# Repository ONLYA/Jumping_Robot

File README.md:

# Jumping_Robot
A robot that is like the RC Jumper in Watch Dogs 2

The updates of the project are in [my blog](https://www.300-300-300-300.space/blog/5/).

In the video above, you can find that there are several functions for the jumpers to achieve:
* Compact
* RF controlled
* "Tank" moving
* Jumping (with "enhanced spring", it can jump over a wall)
* Rotation-free web camera
* Robot arms
* Middle-Man network
* Automatic recognizing the 3D position

There are more functions that it has:
* Items dropping (unlikely to be considered this time!)
* Broadcasting some sound (Maybe included)

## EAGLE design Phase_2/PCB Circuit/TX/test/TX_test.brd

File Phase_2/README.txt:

# PHASE 2
+----------------------------------------------------------+
|                 PHASE 2 - REMOTE CONTROL                 |
+----------------------------------------------------------+
|                  Overview Block Diagram                  |
+----------------------------------------------------------+
 Si4663F30        Si4663F30                MSP430G2553IN20
+----------+   +-------------+          +------------------+
|          <---+             |8-bit GPIO|                  |
| Reciever |RF | Transmitter <----------+ Data Auto-Sender |
|          +--->             <----------+                  |
+----------+   +----------^--+State_SEL +---+----^---------+
                          |                 |    |
                          +-----------------+    |
+---------------------------+  INT/DONE          |
|    Possible Ideas:        |           +--------+---------+
| 1. The computer only      |           |     Joystick     |
|    sends the image        |           |    (Via ADC10)   |
|    coordination data      |           |                  |
| 2. Computer processes     |           +------------------+
|    the data & sends       |           |     Computer     |
|    the preocessed data.   |           |    (Via SPI)     |
|                           |           |                  |
+---------------------------+           +------------------+
+----------------------------------------------------------+
|               Si4663 Interfacing Diagram                 |
+----------------------------------------------------------+
+--------+  +----------------------------------------------+
|        <==>SPI                                           |
| Si4663 |  |                            MSP430G2553       |
|        +-->INT                                           |
+--------+  +----------------------------------------------+
+----------------------------------------------------------+
## API
All of the API functions processed by MSP430 for Si4663 are
regarded to the official programming guide, which can be
downloaded in the current folder.
## Ideas
The basic ideas of this phase can be summarised into points:
1. Special modules for RF transcieving
2. A specialised module to send the sensed data to the RF module
## Components
1. [Si4663F30](https://www.aliexpress.com/item/32816312908.html "Link to buy Si4663F30, a more powerful RF module")
2. MSP430G2553IN20
3. Joystick
4. Computer
5. [USB-to-SPI interface] ... Not found one, try UART probably.
## Test
Still waiting for the delivery...

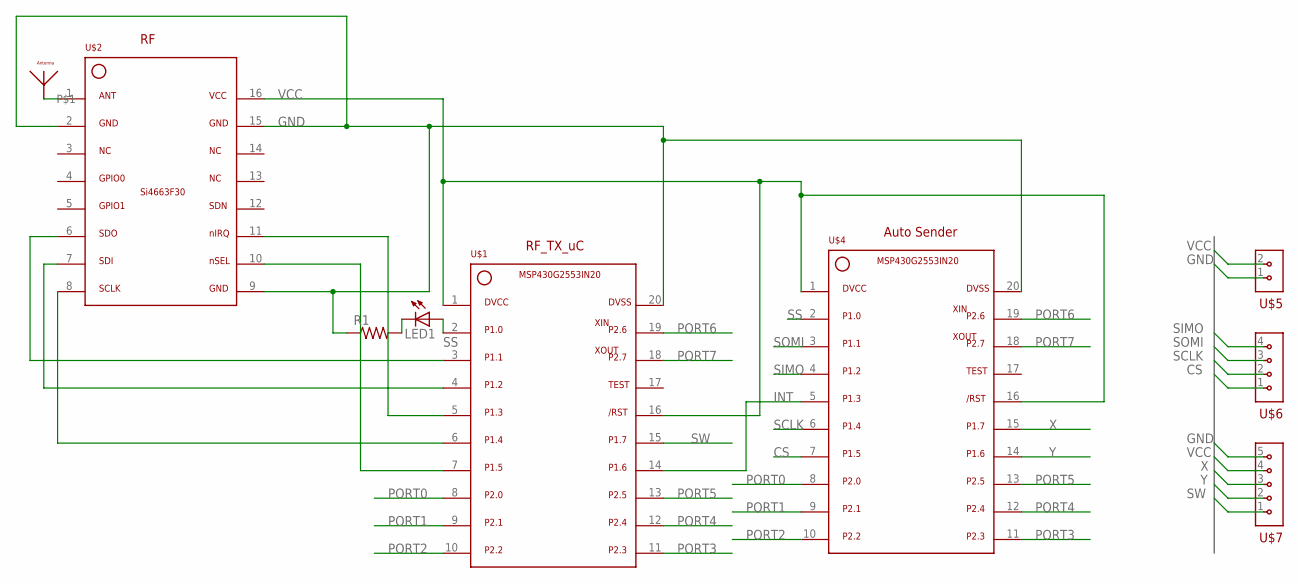
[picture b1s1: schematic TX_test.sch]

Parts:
LED1: LED3MM
R1: R-US_0204/7; 0204/7
U$1, U$4: MSP430G2553IN20; DIP762W53P254L2215H508Q20B
U$2: SI4663F30SI4663F30-3D; INDCAV400P3800X2000X400-16N
U$3: ANTENNA
U$5: H1X2; HDRVR2W64P254_1X2_1016X508X254B
U$6: H1X4; HDRRAR4W64P254_1X4_1016X736X556B
U$7: H1X5; HDRRAR5W64P254_1X5_1016X736X556B

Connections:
CS: U$4.7, U$6.1
GND: R1.1, U$1.20, U$2.2, U$2.9, U$2.15, U$4.20, U$5.1, U$7.5
INT: U$1.14, U$4.5
unnamed: U$2.1, U$3.P$1
unnamed: U$1.7, U$2.10
unnamed: U$1.3, U$2.6
unnamed: U$1.4, U$2.7
unnamed: U$1.6, U$2.8
unnamed: U$1.5, U$2.11
unnamed: LED1.K (C), R1.2
PORT0: U$1.8, U$4.8
PORT1: U$1.9, U$4.9
PORT2: U$1.10, U$4.10
PORT3: U$1.11, U$4.11
PORT4: U$1.12, U$4.12
PORT5: U$1.13, U$4.13
PORT6: U$1.19, U$4.19
PORT7: U$1.18, U$4.18
SCLK: U$4.6, U$6.2
SIMO: U$4.4, U$6.4
SOMI: U$4.3, U$6.3
SS: LED1.A, U$1.2, U$4.2
SW: U$1.15, U$7.1
VCC: U$1.1, U$1.16, U$2.16, U$4.1, U$4.16, U$5.2, U$7.4
X: U$4.15, U$7.3
Y: U$4.14, U$7.2

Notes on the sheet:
RF_TX_uC
Auto Sender

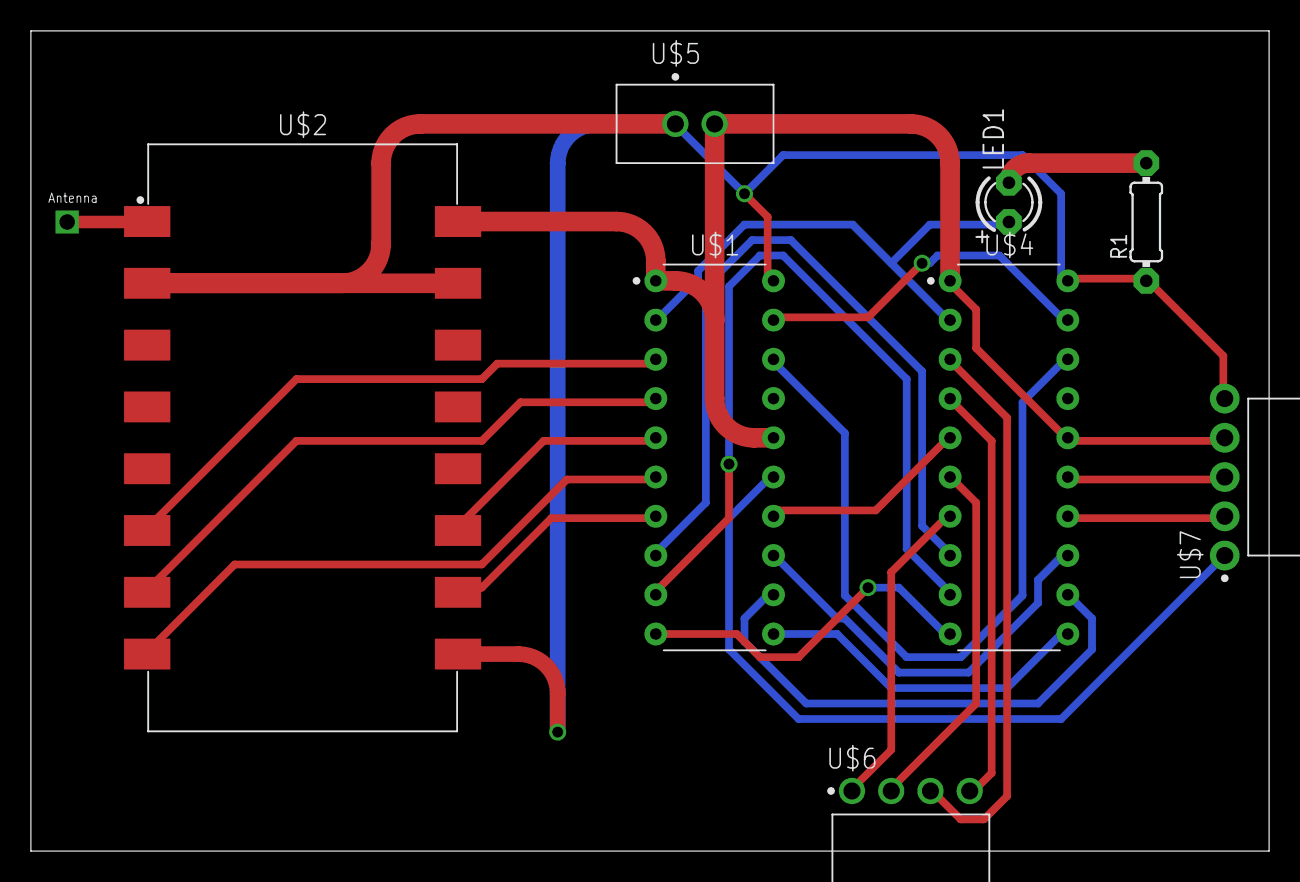
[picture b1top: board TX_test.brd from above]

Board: 2 copper layers, 80.2 x 53.1 mm, 9 parts (0 on the bottom side), 26 nets.

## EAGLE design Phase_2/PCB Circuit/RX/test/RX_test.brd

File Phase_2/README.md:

# PHASE 2
```
+----------------------------------------------------------+
|                 PHASE 2 - REMOTE CONTROL                 |
+----------------------------------------------------------+
|                  Overview Block Diagram                  |
+----------------------------------------------------------+
 Si4663F30        Si4663F30                MSP430G2553IN20
+----------+   +-------------+          +------------------+
|          <---+             |8-bit GPIO|                  |
| Reciever |RF | Transmitter <----------+ Data Auto-Sender |
|          +--->             <----------+                  |
+----------+   +----------^--+State_SEL +---+----^---------+
                          |                 |    |
                          +-----------------+    |
+---------------------------+  INT/DONE          |
|    Possible Ideas:        |           +--------+---------+
| 1. The computer only      |           |     Joystick     |
|    sends the image        |           |    (Via ADC10)   |
|    coordination data      |           |                  |
| 2. Computer processes     |           +------------------+
|    the data & sends       |           |     Computer     |
|    the preocessed data.   |           |    (Via SPI)     |
|                           |           |                  |
+---------------------------+           +------------------+
+----------------------------------------------------------+
|               Si4663 Interfacing Diagram                 |
+----------------------------------------------------------+
+--------+  +----------------------------------------------+
|        <==>SPI                                           |
| Si4663 |  |                            MSP430G2553       |
|        +-->INT                                           |
+--------+  +----------------------------------------------+
+----------------------------------------------------------+
```
## API
All of the API functions processed by MSP430 for Si4663 are
regarded to the official programming guide, which can be
downloaded in the current folder.
## Ideas
The basic ideas of this phase can be summarised into points:
1. Special modules for RF transcieving
2. A specialised module to send the sensed data to the RF module
## Components
1. [Si4663F30](https://www.aliexpress.com/item/32816312908.html "Link to buy Si4663F30, a more powerful RF module")
2. MSP430G2553IN20
3. Joystick
4. Computer
5. [USB-to-SPI interface] ... Not found one, try UART probably.
## Test
Still waiting for the delivery...

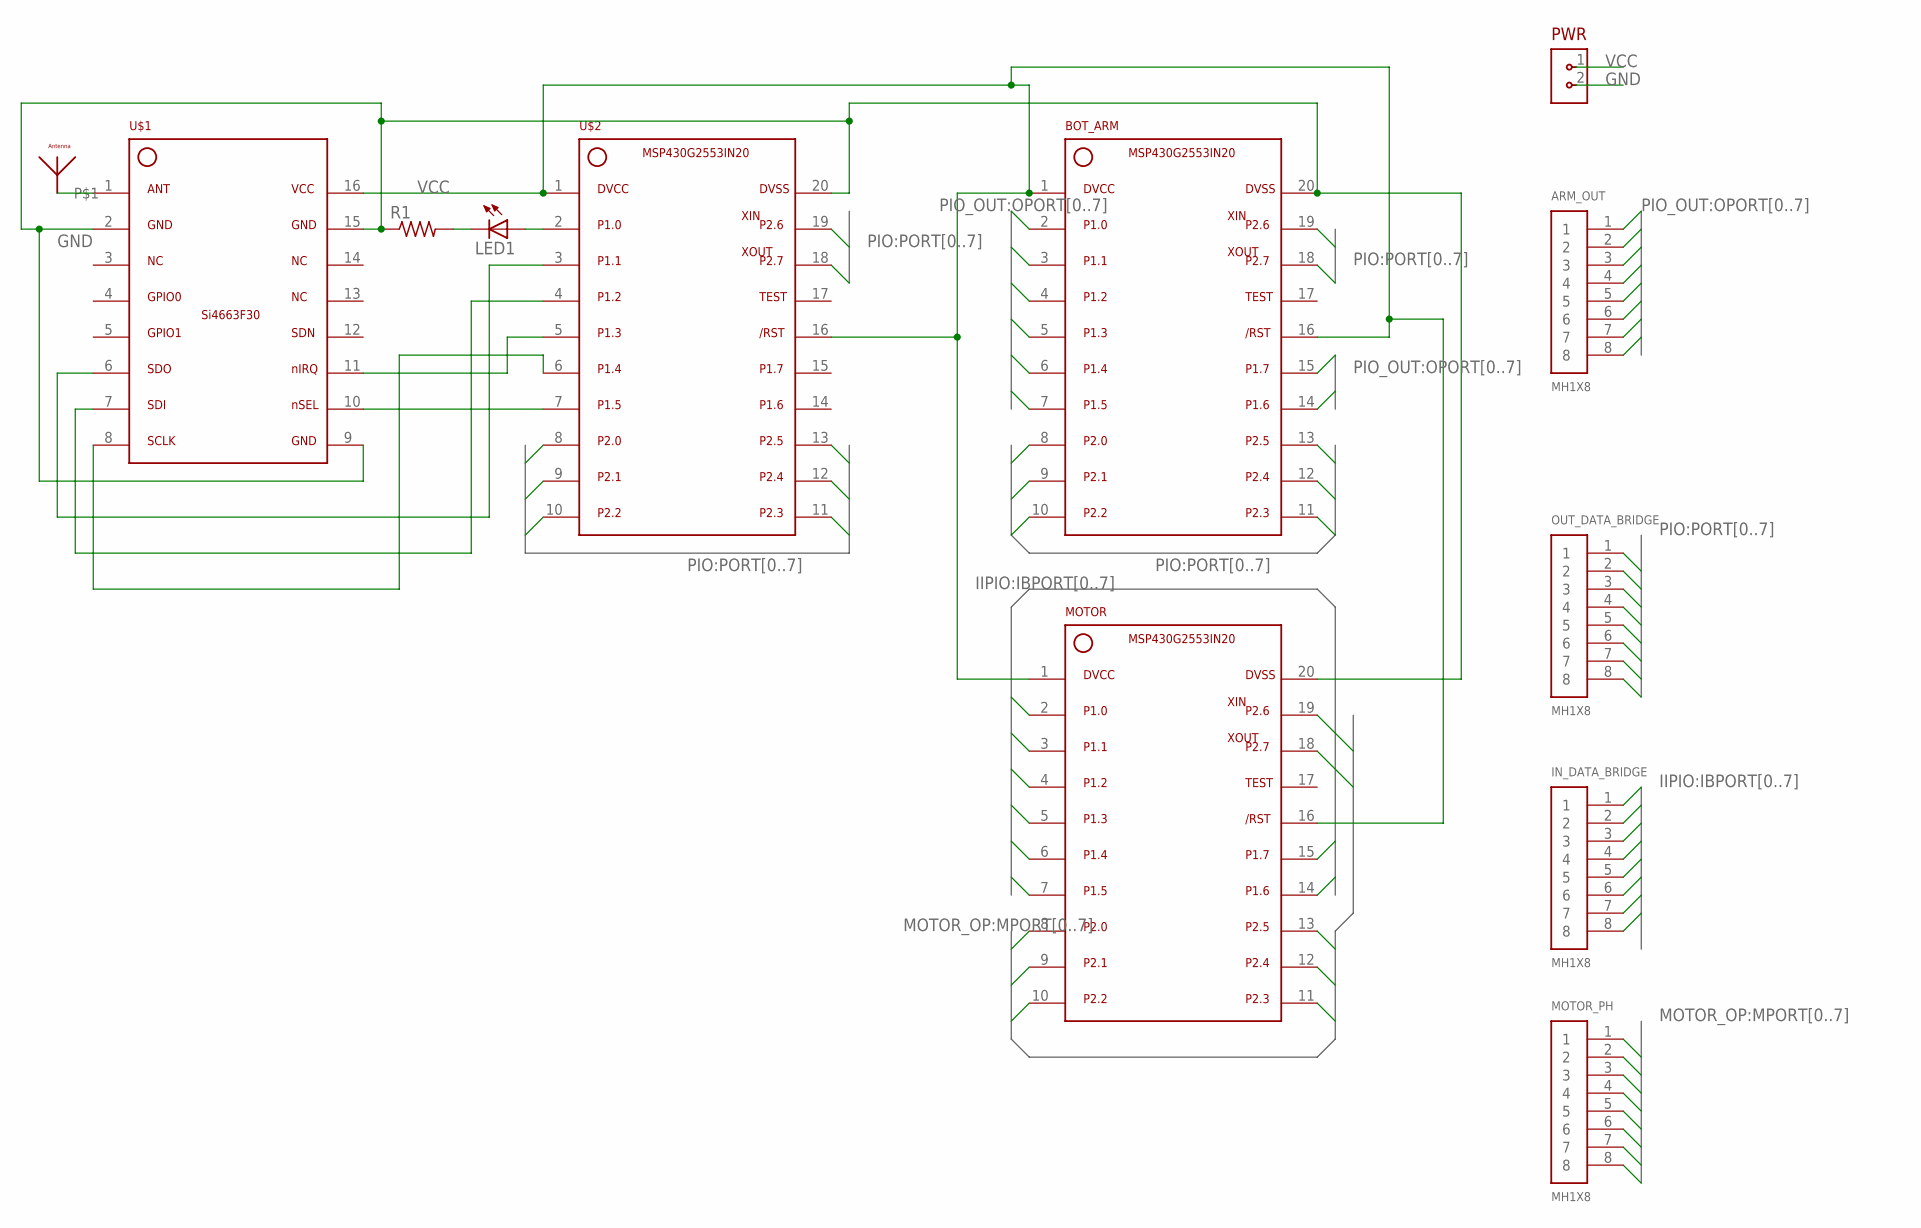
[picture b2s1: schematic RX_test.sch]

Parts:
ARM_OUT: MH1X8; 61300811121
BOT_ARM: MSP430G2553IN20; DIP762W53P254L2215H508Q20B
IN_DATA_BRIDGE: MH1X8; 61300811121
LED1: LED3MM
MOTOR: MSP430G2553IN20; DIP762W53P254L2215H508Q20B
MOTOR_PH: MH1X8; 61300811121
OUT_DATA_BRIDGE: MH1X8; 61300811121
PWR: FH1X2; HDRVR2W64P254_1X2_1016X508X254B
R1: R-US_0204/7; 0204/7
U$1: SI4663F30SI4663F30-3D; INDCAV400P3800X2000X400-16N
U$2: MSP430G2553IN20; DIP762W53P254L2215H508Q20B
U$4: ANTENNA

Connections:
GND: BOT_ARM.20, MOTOR.20, PWR.2, R1.1, U$1.2, U$1.9, U$1.15, U$2.20
IBPORT0: IN_DATA_BRIDGE.1, MOTOR.2
IBPORT1: IN_DATA_BRIDGE.2, MOTOR.3
IBPORT2: IN_DATA_BRIDGE.3, MOTOR.4
IBPORT3: IN_DATA_BRIDGE.4, MOTOR.5
IBPORT4: IN_DATA_BRIDGE.5, MOTOR.6
IBPORT5: IN_DATA_BRIDGE.6, MOTOR.7
IBPORT6: IN_DATA_BRIDGE.7, MOTOR.14
IBPORT7: IN_DATA_BRIDGE.8, MOTOR.15
MPORT0: MOTOR.8, MOTOR_PH.1
MPORT1: MOTOR.9, MOTOR_PH.2
MPORT2: MOTOR.10, MOTOR_PH.3
MPORT3: MOTOR.11, MOTOR_PH.4
MPORT4: MOTOR.12, MOTOR_PH.5
MPORT5: MOTOR.13, MOTOR_PH.6
MPORT6: MOTOR.19, MOTOR_PH.7
MPORT7: MOTOR.18, MOTOR_PH.8
unnamed: LED1.K (C), R1.2
unnamed: LED1.A, U$2.2
unnamed: U$1.1, U$4.P$1
unnamed: U$1.6, U$2.3
unnamed: U$1.7, U$2.4
unnamed: U$1.8, U$2.6
unnamed: U$1.10, U$2.7
unnamed: U$1.11, U$2.5
OPORT0: ARM_OUT.1, BOT_ARM.2
OPORT1: ARM_OUT.2, BOT_ARM.3
OPORT2: ARM_OUT.3, BOT_ARM.4
OPORT3: ARM_OUT.4, BOT_ARM.5
OPORT4: ARM_OUT.5, BOT_ARM.6
OPORT5: ARM_OUT.6, BOT_ARM.7
OPORT6: ARM_OUT.7, BOT_ARM.14
OPORT7: ARM_OUT.8, BOT_ARM.15
PORT0: BOT_ARM.8, OUT_DATA_BRIDGE.1, U$2.8
PORT1: BOT_ARM.9, OUT_DATA_BRIDGE.2, U$2.9
PORT2: BOT_ARM.10, OUT_DATA_BRIDGE.3, U$2.10
PORT3: BOT_ARM.11, OUT_DATA_BRIDGE.4, U$2.11
PORT4: BOT_ARM.12, OUT_DATA_BRIDGE.5, U$2.12
PORT5: BOT_ARM.13, OUT_DATA_BRIDGE.6, U$2.13
PORT6: BOT_ARM.19, OUT_DATA_BRIDGE.7, U$2.19
PORT7: BOT_ARM.18, OUT_DATA_BRIDGE.8, U$2.18
VCC: BOT_ARM.1, BOT_ARM.16, MOTOR.1, MOTOR.16, PWR.1, U$1.16, U$2.1, U$2.16

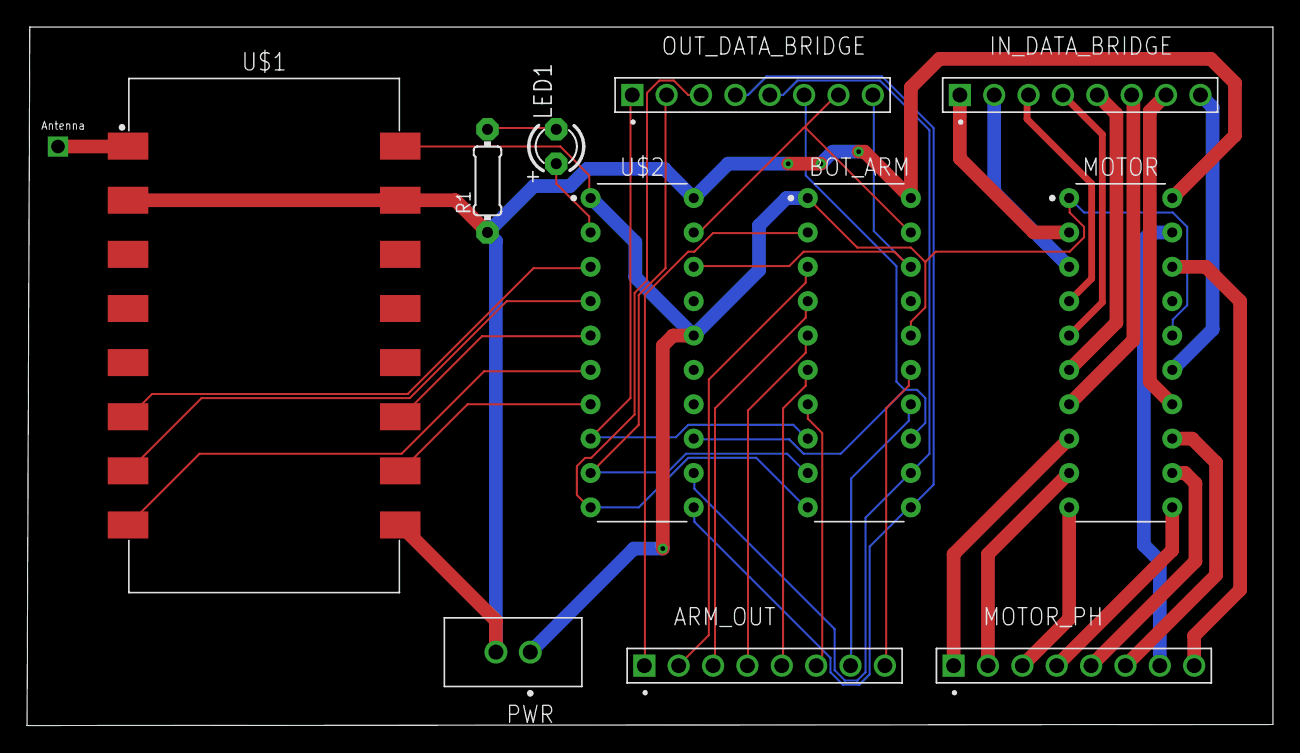
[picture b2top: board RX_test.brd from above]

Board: 2 copper layers, 92.1 x 51.6 mm, 12 parts (0 on the bottom side), 42 nets.

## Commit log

2019-06-09 software update
2019-06-09 finished
2019-06-09 Temp_Final
2019-06-12 Controller and Demo_CTRL for Phase 1
2019-06-13 Improved Software
2019-06-20 Circuits + Gearbox
2019-06-21 3-gen Mech Design
2019-07-08 GEARBOX Finished with stl
2019-07-09 Software description
2019-08-07 Phase 2 init
2019-08-27 Phase 3 init
2019-09-05 Rename README.txt to README.md
2019-09-23 Phase 2 Softtware update
2021-07-02 JoyStick example updated
